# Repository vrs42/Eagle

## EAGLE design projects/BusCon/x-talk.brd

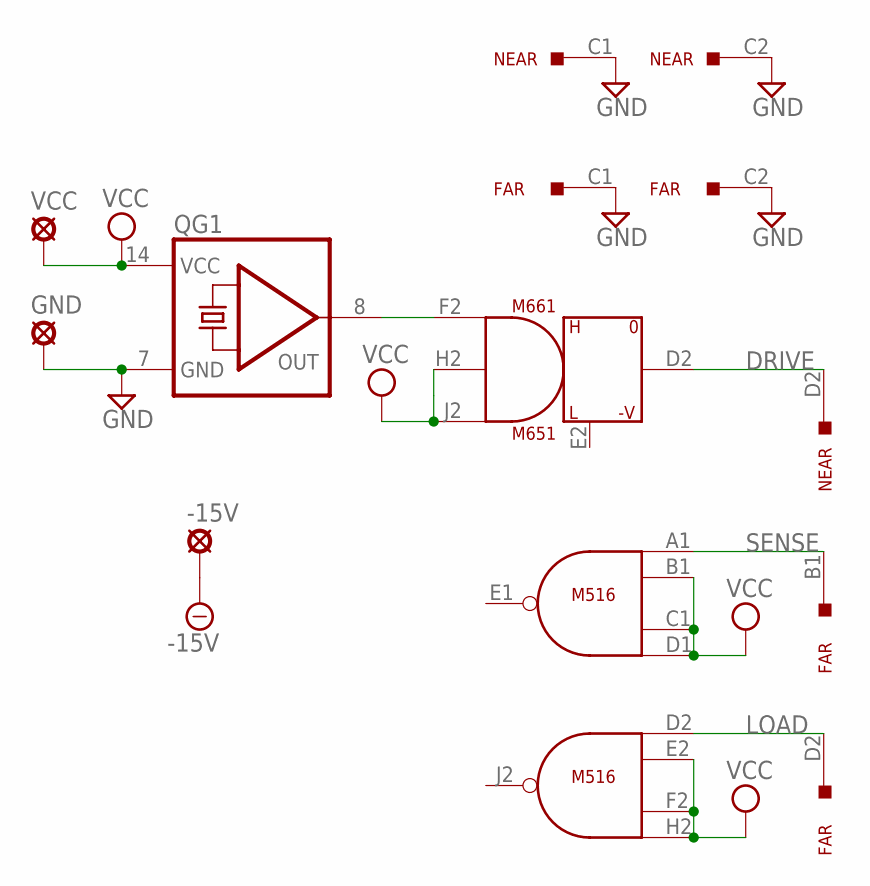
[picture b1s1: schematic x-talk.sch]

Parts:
-15V: SE11
FAR: M916; H807
GND: SE11
M516: M117; H807
M661: M651; H807
NEAR: M916; H807
QG1: QG5860; DIL14S
VCC: SE11

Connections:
-15V: -15V.MP, M661.B2 (-15V)
DRIVE: M661.D2 (OUT), NEAR.D2
GND: FAR.C1, FAR.C2, GND.MP, M516.C2 (GND), M516.T1 (GND), M661.C2 (GND), NEAR.C1, NEAR.C2, QG1.7 (GND)
LOAD: FAR.D2, M516.D2 (IN1)
unnamed: M661.F2 (IN1), QG1.8 (OUT)
SENSE: FAR.B1, M516.A1 (IN1)
VCC: M516.A2 (VCC), M516.B1 (IN2), M516.C1 (IN3), M516.D1 (IN4), M516.E2 (IN2), M516.F2 (IN3), M516.H2 (IN4), M661.A2 (VCC), M661.H2 (IN2), M661.J2 (IN3), QG1.14 (VCC), VCC.MP

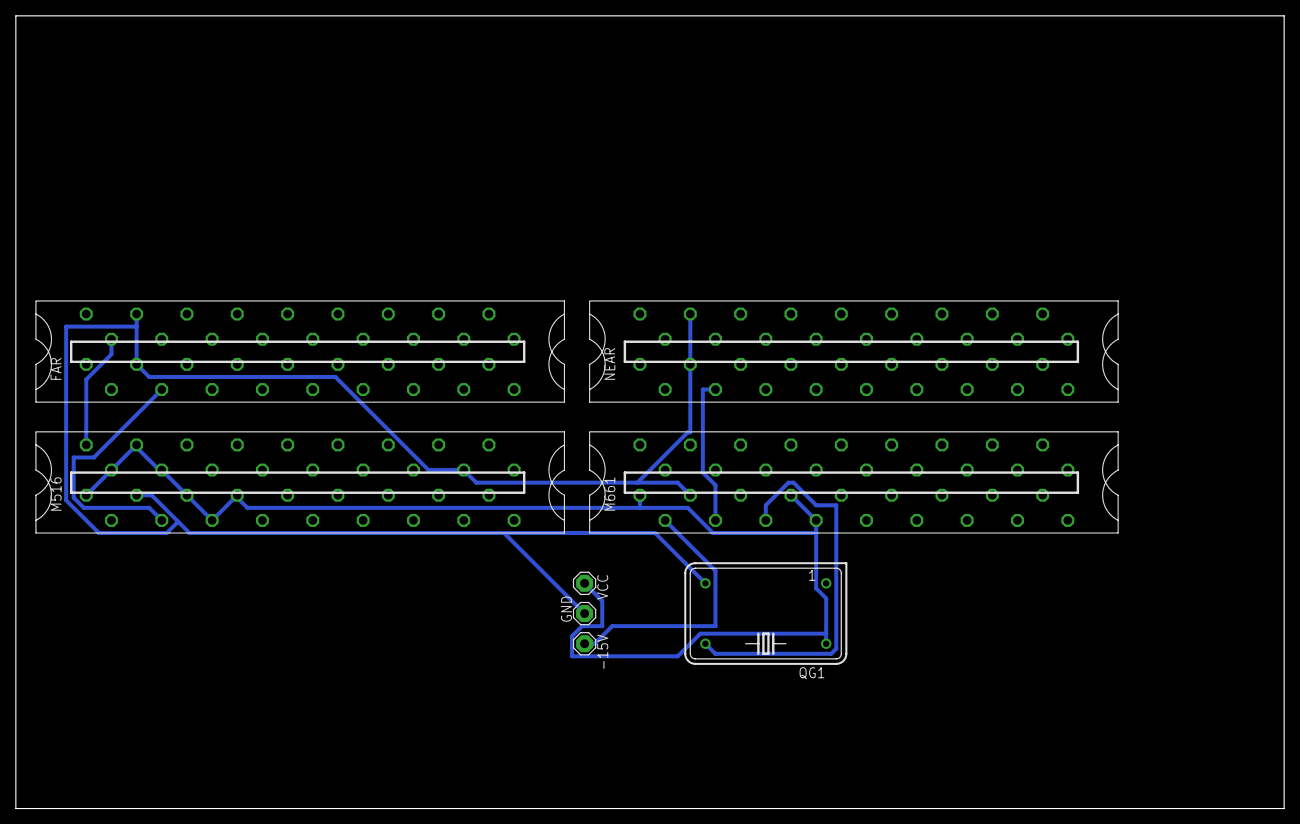
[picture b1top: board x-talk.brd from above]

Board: 2 copper layers, 160.0 x 100.0 mm, 8 parts (0 on the bottom side), 7 nets.

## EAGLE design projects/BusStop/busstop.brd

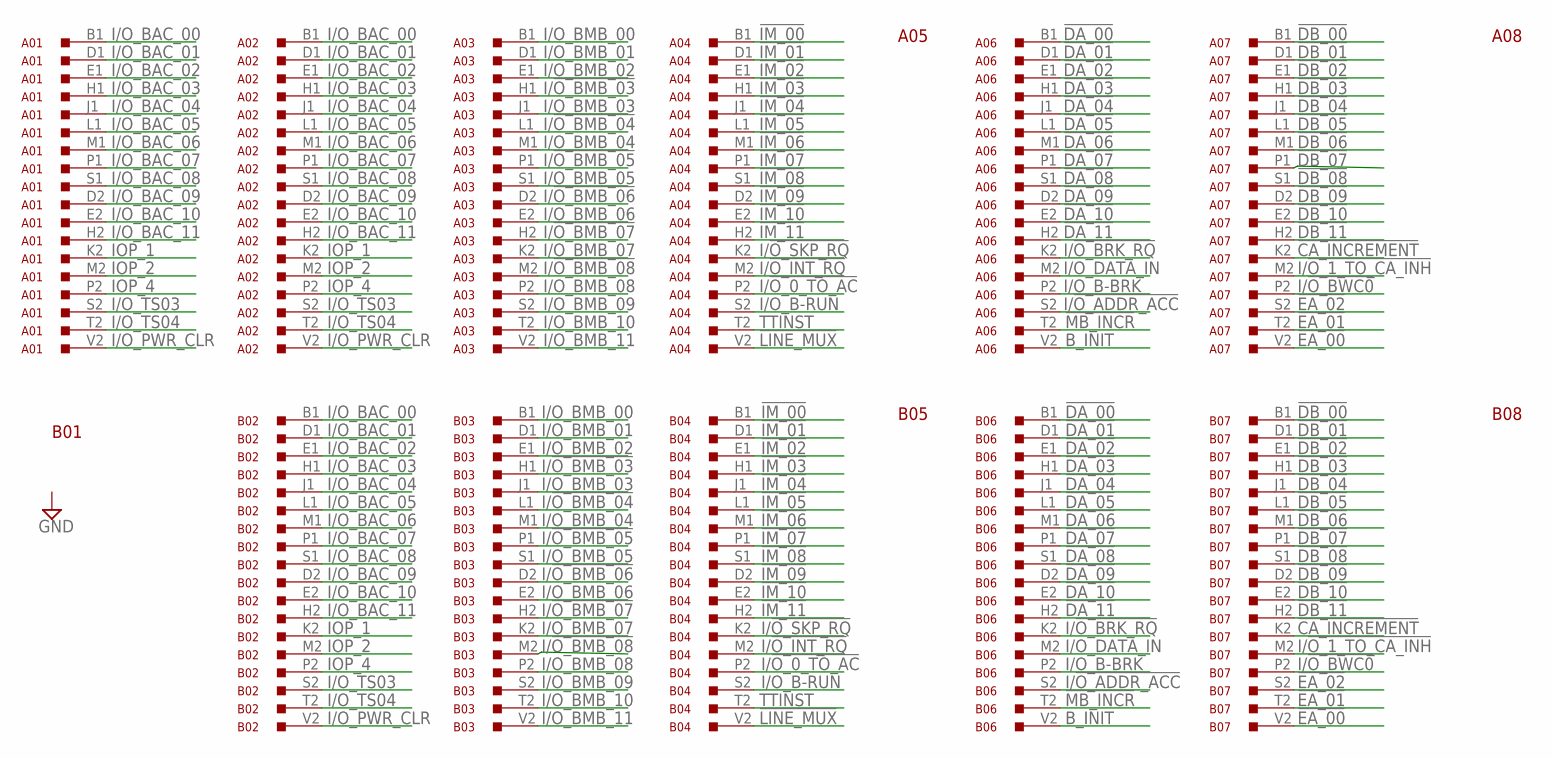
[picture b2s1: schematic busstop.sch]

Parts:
A01: G717; H807
A02, A03, A04, A06, A07: M903; H807
A05, A08: H807
B01, B05, B08: H807
B02, B03, B04, B06, B07: M903; H807

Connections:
!CA_INCREMENT: A07.K2, B07.K2
!DA_00: A06.B1, B06.B1
!DA_01: A06.D1, B06.D1
!DA_02: A06.E1, B06.E1
!DA_03: A06.H1, B06.H1
!DA_04: A06.J1, B06.J1
!DA_05: A06.L1, B06.L1
!DA_06: A06.M1, B06.M1
!DA_07: A06.P1, B06.P1
!DA_08: A06.S1, B06.S1
!DA_09: A06.D2, B06.D2
!DA_10: A06.E2, B06.E2
!DA_11: A06.H2, B06.H2
!DB_00: A07.B1, B07.B1
!DB_01: A07.D1, B07.D1
!DB_02: A07.E1, B07.E1
!DB_03: A07.H1, B07.H1
!DB_04: A07.J1, B07.J1
!DB_05: A07.L1, B07.L1
!DB_06: A07.M1, B07.M1
!DB_07: A07.P1, B07.P1
!DB_08: A07.S1, B07.S1
!DB_09: A07.D2, B07.D2
!DB_10: A07.E2, B07.E2
!DB_11: A07.H2, B07.H2
!EA_00: A07.V2, B07.V2
!EA_01: A07.T2, B07.T2
!EA_02: A07.S2, B07.S2
!IM_00: A04.B1, B04.B1
!IM_01: A04.D1, B04.D1
!IM_02: A04.E1, B04.E1
!IM_03: A04.H1, B04.H1
!IM_04: A04.J1, B04.J1
!IM_05: A04.L1, B04.L1
!IM_06: A04.M1, B04.M1
!IM_07: A04.P1, B04.P1
!IM_08: A04.S1, B04.S1
!IM_09: A04.D2, B04.D2
!IM_10: A04.E2, B04.E2
!IM_11: A04.H2, B04.H2
!LINE_MUX: A04.V2, B04.V2
!MB_INCR: A06.T2, B06.T2
B_INIT: A06.V2, B06.V2
GND: A01.A1 (GND), A01.C1 (GND), A01.C2 (GND), A01.F1 (GND), A01.F2 (GND), A01.J2 (GND), A01.K1 (GND), A01.L2 (GND), A01.N1 (GND), A01.N2 (GND), A01.R1 (GND), A01.R2 (GND), A01.T1 (GND), A01.U2 (GND), A02.A1 (GND), A02.C1 (GND), A02.C2 (GND), A02.F1 (GND), A02.F2 (GND), A02.J2 (GND), A02.K1 (GND), A02.L2 (GND), A02.N1 (GND), A02.N2 (GND), A02.R1 (GND), A02.R2 (GND), A02.T1 (GND), A02.U2 (GND), A03.A1 (GND), A03.C1 (GND), A03.C2 (GND), A03.F1 (GND), A03.F2 (GND), A03.J2 (GND), A03.K1 (GND), A03.L2 (GND), A03.N1 (GND), A03.N2 (GND), A03.R1 (GND), A03.R2 (GND), A03.T1 (GND), A03.U2 (GND), A04.A1 (GND), A04.C1 (GND), A04.C2 (GND), A04.F1 (GND), A04.F2 (GND), A04.J2 (GND), A04.K1 (GND), A04.L2 (GND), A04.N1 (GND), A04.N2 (GND), A04.R1 (GND), A04.R2 (GND), A04.T1 (GND), A04.U2 (GND), A06.A1 (GND), A06.C1 (GND), A06.C2 (GND), A06.F1 (GND), A06.F2 (GND), A06.J2 (GND), A06.K1 (GND), A06.L2 (GND), A06.N1 (GND), A06.N2 (GND), A06.R1 (GND), A06.R2 (GND), A06.T1 (GND), A06.U2 (GND), A07.A1 (GND), A07.C1 (GND), A07.C2 (GND), A07.F1 (GND), A07.F2 (GND), A07.J2 (GND), A07.K1 (GND), A07.L2 (GND), A07.N1 (GND), A07.N2 (GND), A07.R1 (GND), A07.R2 (GND), A07.T1 (GND), A07.U2 (GND), B02.A1 (GND), B02.C1 (GND), B02.C2 (GND), B02.F1 (GND), B02.F2 (GND), B02.J2 (GND), B02.K1 (GND), B02.L2 (GND), B02.N1 (GND), B02.N2 (GND), B02.R1 (GND), B02.R2 (GND), B02.T1 (GND), B02.U2 (GND), B03.A1 (GND), B03.C1 (GND), B03.C2 (GND), B03.F1 (GND), B03.F2 (GND), B03.J2 (GND), B03.K1 (GND), B03.L2 (GND), B03.N1 (GND), B03.N2 (GND), B03.R1 (GND), B03.R2 (GND), B03.T1 (GND), B03.U2 (GND), B04.A1 (GND), B04.C1 (GND), B04.C2 (GND), B04.F1 (GND), B04.F2 (GND), B04.J2 (GND), B04.K1 (GND), B04.L2 (GND), B04.N1 (GND), B04.N2 (GND), B04.R1 (GND), B04.R2 (GND), B04.T1 (GND), B04.U2 (GND), B06.A1 (GND), B06.C1 (GND), B06.C2 (GND), B06.F1 (GND), B06.F2 (GND), B06.J2 (GND), B06.K1 (GND), B06.L2 (GND), B06.N1 (GND), B06.N2 (GND), B06.R1 (GND), B06.R2 (GND), B06.T1 (GND), B06.U2 (GND), B07.A1 (GND), B07.C1 (GND), B07.C2 (GND), B07.F1 (GND), B07.F2 (GND), B07.J2 (GND), B07.K1 (GND), B07.L2 (GND), B07.N1 (GND), B07.N2 (GND), B07.R1 (GND), B07.R2 (GND), B07.T1 (GND), B07.U2 (GND)
I/!O_0_TO_AC: A04.P2, B04.P2
I/!O_1_TO_CA_INH: A07.M2, B07.M2
I/!O_ADDR_ACC: A06.S2, B06.S2
I/!O_BMB_03: A03.H1, B03.H1
I/!O_BMB_04: A03.L1, B03.L1
I/!O_BMB_05: A03.P1, B03.P1
I/!O_BMB_06: A03.D2, B03.D2
I/!O_BMB_07: A03.H2, B03.H2
I/!O_BMB_08: A03.M2, B03.M2
I/!O_BRK_RQ: A06.K2, B06.K2
I/!O_BWC0: A07.P2, B07.P2
I/!O_INT_RQ: A04.M2, B04.M2
I/!O_SKP_RQ: A04.K2, B04.K2
I/O_B-BRK: A06.P2, B06.P2
I/O_B-RUN: A04.S2, B04.S2
I/O_BAC_00: A01.B1, A02.B1, B02.B1
I/O_BAC_01: A01.D1, A02.D1, B02.D1
I/O_BAC_02: A01.E1, A02.E1, B02.E1
I/O_BAC_03: A01.H1, A02.H1, B02.H1
I/O_BAC_04: A01.J1, A02.J1, B02.J1
I/O_BAC_05: A01.L1, A02.L1, B02.L1
I/O_BAC_06: A01.M1, A02.M1, B02.M1
I/O_BAC_07: A01.P1, A02.P1, B02.P1
I/O_BAC_08: A01.S1, A02.S1, B02.S1
I/O_BAC_09: A01.D2, A02.D2, B02.D2
I/O_BAC_10: A01.E2, A02.E2, B02.E2
I/O_BAC_11: A01.H2, A02.H2, B02.H2
I/O_BMB_00: A03.B1, B03.B1
I/O_BMB_01: A03.D1, B03.D1
I/O_BMB_02: A03.E1, B03.E1
I/O_BMB_03: A03.J1, B03.J1
I/O_BMB_04: A03.M1, B03.M1
I/O_BMB_05: A03.S1, B03.S1
I/O_BMB_06: A03.E2, B03.E2
I/O_BMB_07: A03.K2, B03.K2
I/O_BMB_08: A03.P2, B03.P2
I/O_BMB_09: A03.S2, B03.S2
I/O_BMB_10: A03.T2, B03.T2
I/O_BMB_11: A03.V2, B03.V2
I/O_DATA_IN: A06.M2, B06.M2
I/O_PWR_CLR: A01.V2, A02.V2, B02.V2
I/O_TS03: A01.S2, A02.S2, B02.S2
I/O_TS04: A01.T2, A02.T2, B02.T2
IOP_1: A01.K2, A02.K2, B02.K2
IOP_2: A01.M2, A02.M2, B02.M2
IOP_4: A01.P2, A02.P2, B02.P2
TTINST: A04.T2, B04.T2

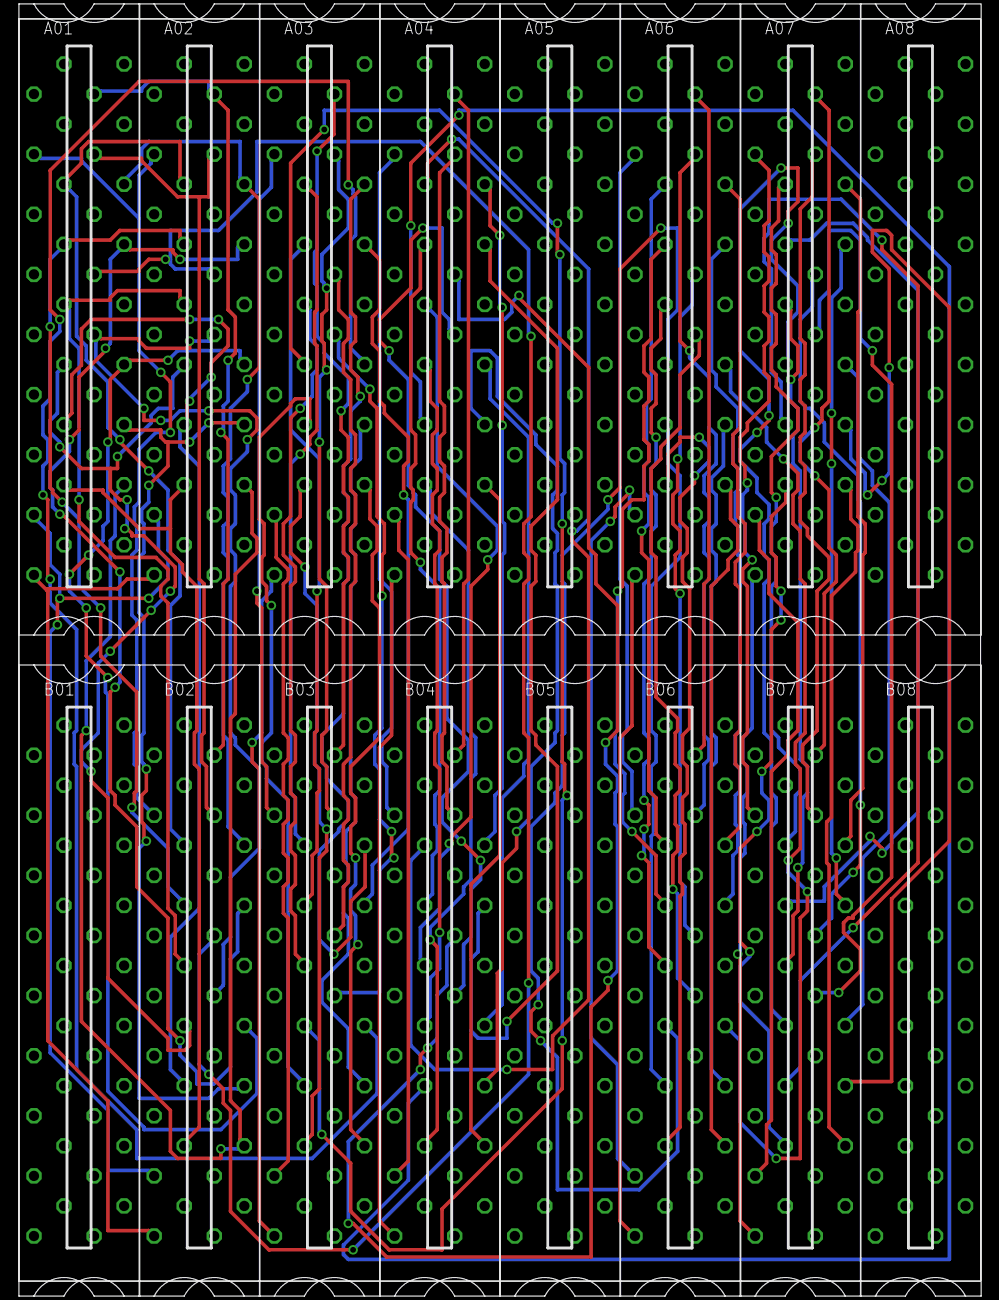
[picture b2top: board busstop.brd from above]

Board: 3 copper layers, 101.6 x 133.3 mm, 18 parts (0 on the bottom side), 91 nets.

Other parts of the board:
U$5, U$6: CBLOCK

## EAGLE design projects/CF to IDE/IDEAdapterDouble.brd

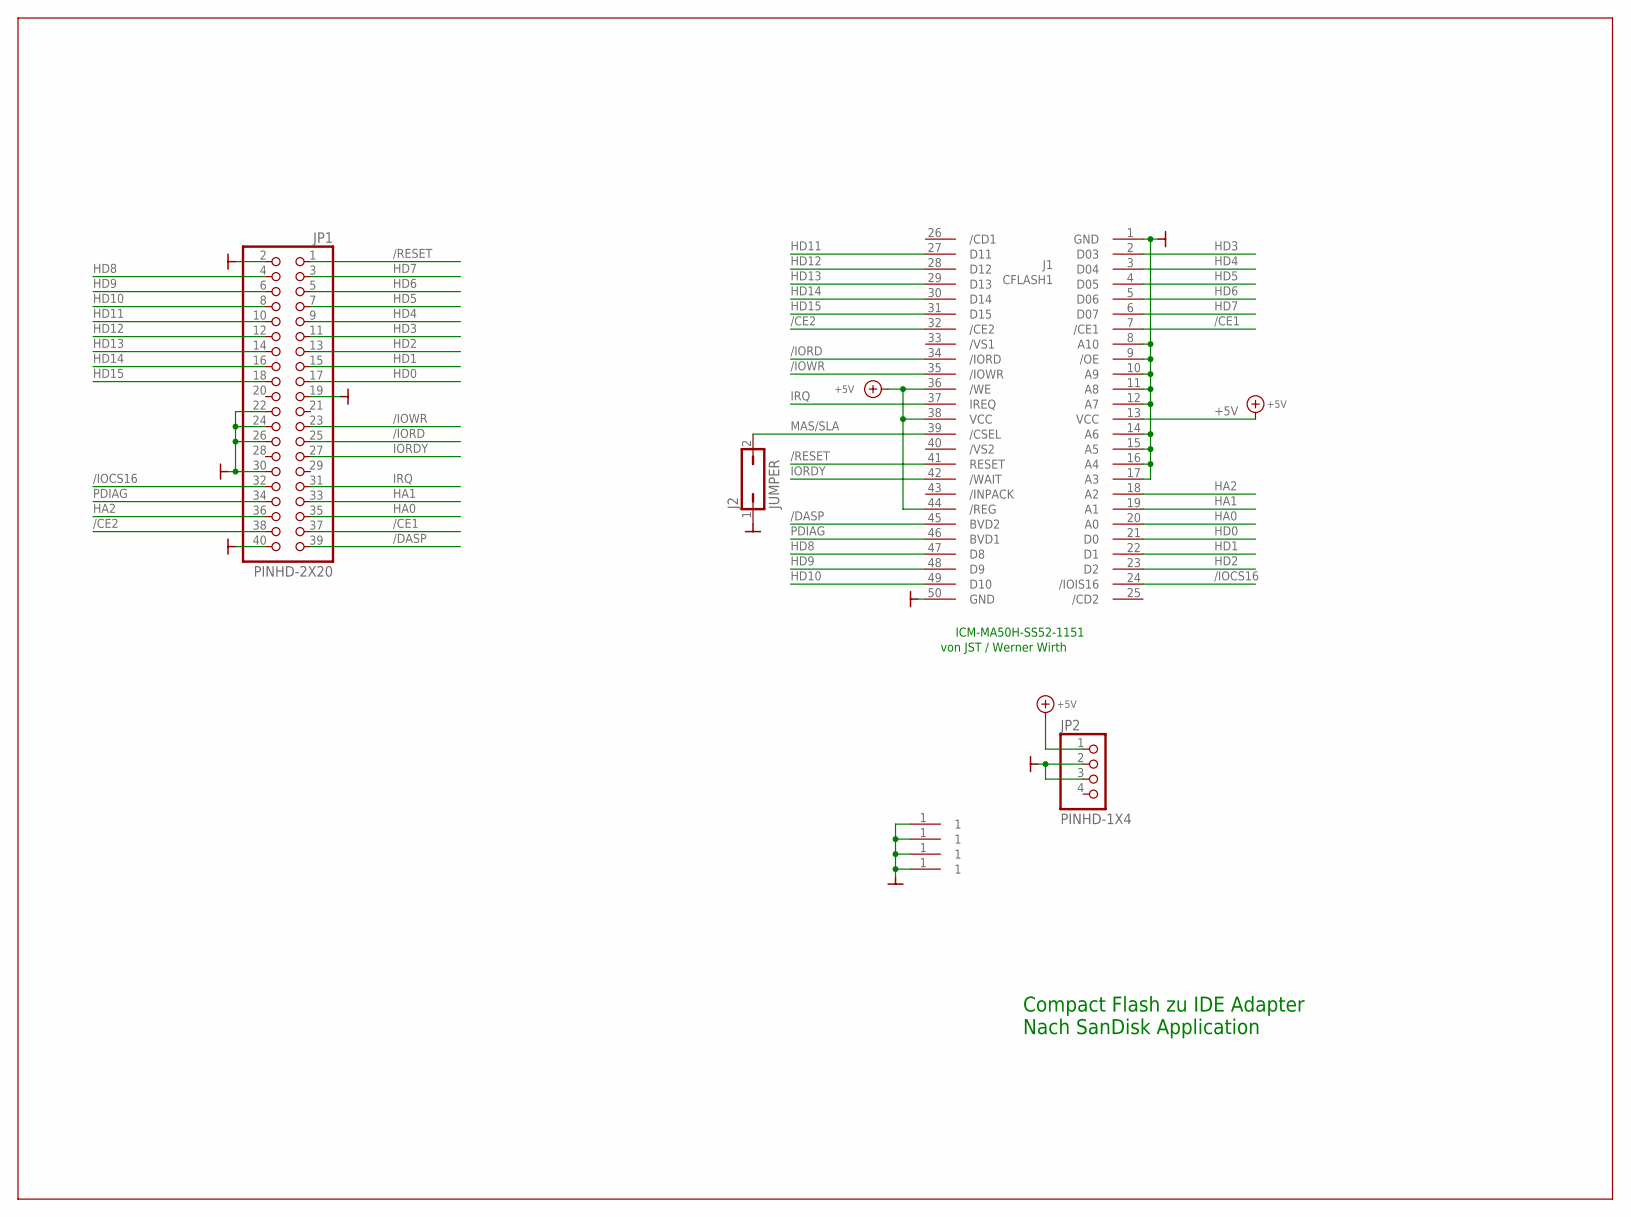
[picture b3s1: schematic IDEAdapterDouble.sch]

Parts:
J1: CFLASH1; CFSMT
J2: JUMPER; JP1
JP1: PINHD-2X20; 2X20
JP2: PINHD-1X4; 1X04
U$13, U$14, U$16, U$17: BOHRUNG

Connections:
+5V: J1.13 (VCC), J1.36 (/WE), J1.38 (VCC), J1.44 (/REG), JP2.1
/CE1: J1.7 (/CE1), JP1.37
/CE2: J1.32 (/CE2), JP1.38
/DASP: J1.45 (BVD2), JP1.39
/IOCS16: J1.24 (/IOIS16), JP1.32
/IORD: J1.34 (/IORD), JP1.25
/IOWR: J1.35 (/IOWR), JP1.23
/RESET: J1.41 (RESET), JP1.1
GND: J1.1 (GND), J1.8 (A10), J1.9 (/OE), J1.10 (A9), J1.11 (A8), J1.12 (A7), J1.14 (A6), J1.15 (A5), J1.16 (A4), J1.17 (A3), J1.50 (GND), J2.1, JP1.2, JP1.19, JP1.22, JP1.24, JP1.26, JP1.30, JP1.40, JP2.2, JP2.3, U$13.1, U$14.1, U$16.1, U$17.1
HA0: J1.20 (A0), JP1.35
HA1: J1.19 (A1), JP1.33
HA2: J1.18 (A2), JP1.36
HD0: J1.21 (D0), JP1.17
HD1: J1.22 (D1), JP1.15
HD2: J1.23 (D2), JP1.13
HD3: J1.2 (D03), JP1.11
HD4: J1.3 (D04), JP1.9
HD5: J1.4 (D05), JP1.7
HD6: J1.5 (D06), JP1.5
HD7: J1.6 (D07), JP1.3
HD8: J1.47 (D8), JP1.4
HD9: J1.48 (D9), JP1.6
HD10: J1.49 (D10), JP1.8
HD11: J1.27 (D11), JP1.10
HD12: J1.28 (D12), JP1.12
HD13: J1.29 (D13), JP1.14
HD14: J1.30 (D14), JP1.16
HD15: J1.31 (D15), JP1.18
IORDY: J1.42 (/WAIT), JP1.27
IRQ: J1.37 (IREQ), JP1.31
MAS/SLA: J1.39 (/CSEL), J2.2
PDIAG: J1.46 (BVD1), JP1.34

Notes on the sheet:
Compact Flash zu IDE Adapter
Nach SanDisk Application
ICM-MA50H-SS52-1151
von JST / Werner Wirth

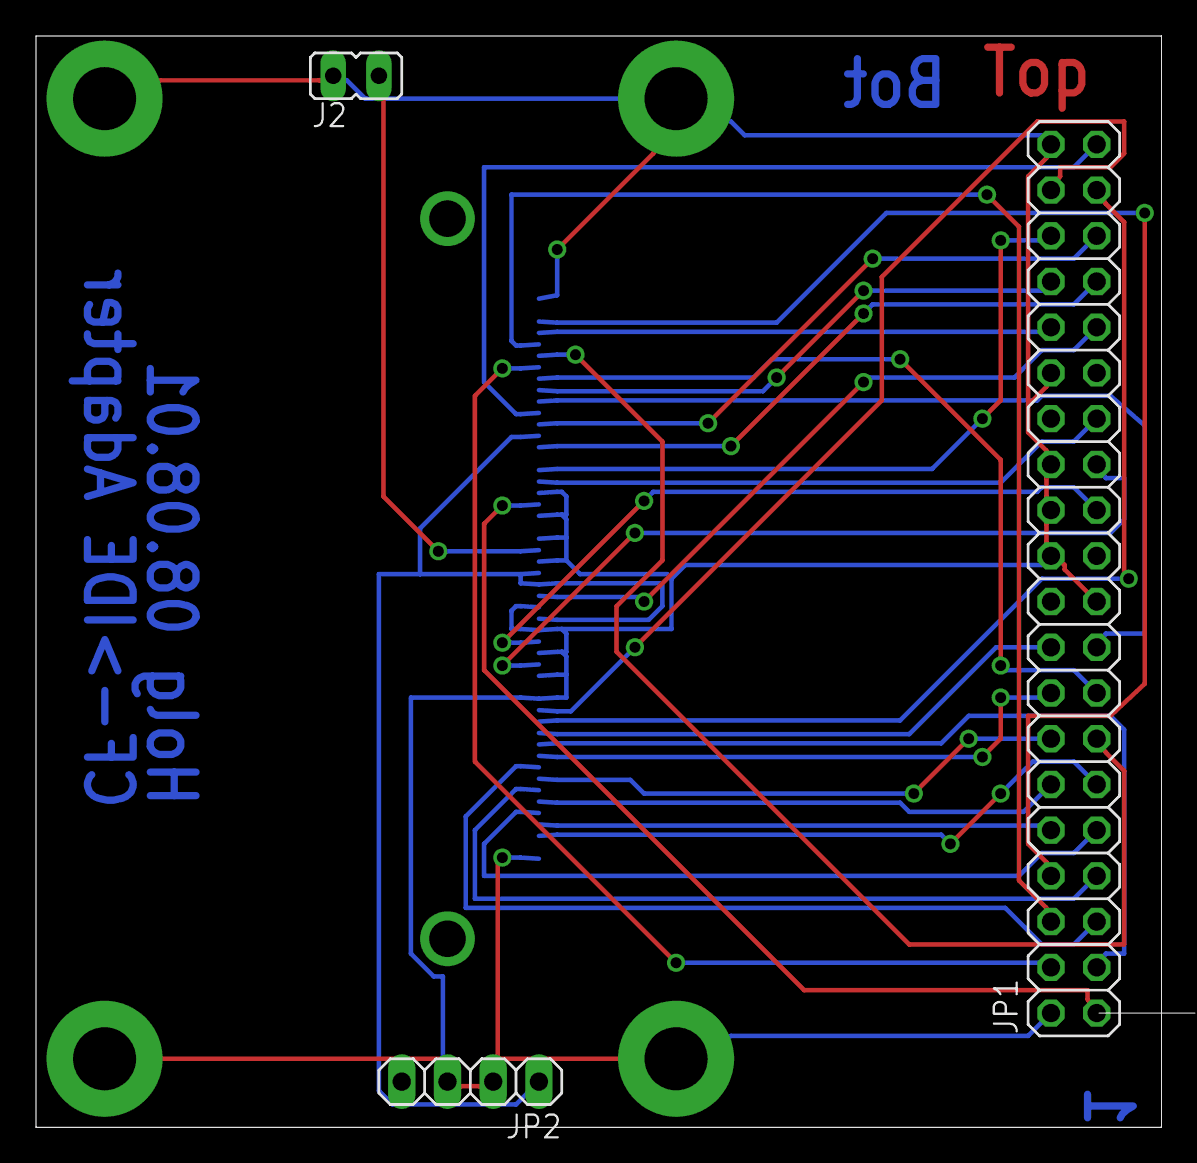
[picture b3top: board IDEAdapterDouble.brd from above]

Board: 2 copper layers, 62.5 x 60.6 mm, 8 parts (1 on the bottom side), 32 nets.

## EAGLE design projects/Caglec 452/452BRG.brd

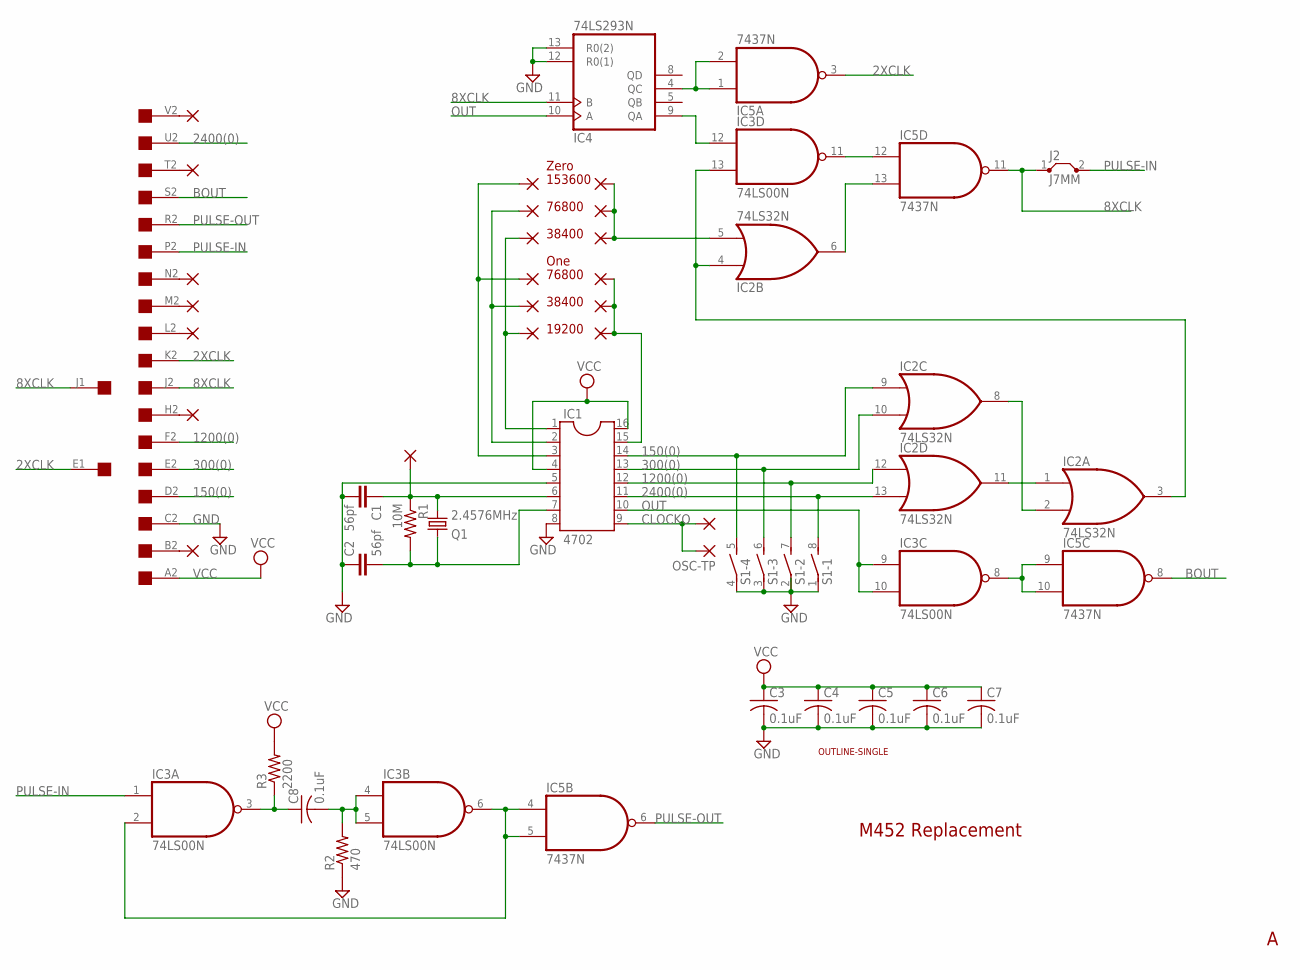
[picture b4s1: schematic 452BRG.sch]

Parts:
C1, C2: 56pf; C075-032X103
C3, C4, C5, C6, C7, C8: 0.1uF; C075-032X103
IC1: 4702; DIL16
IC2: 74LS32N; DIL14
IC3: 74LS00N; DIL14
IC4: 74LS293N; DIL14
IC5: 7437N; DIL14
J2: J7MM; 07
OSC-TP: 1,6/0,8
PAD1, PAD2, PAD3, PAD4, PAD5, PAD6, PAD7, PAD8, PAD9, PAD10, PAD11, PAD12, PAD13, PAD14, PAD15, PAD16, PAD17, PAD18, PAD19, PAD20: 1,6/0,8
Q1: 2.4576MHz; HC49U-H
R1: 10M; 0207/10
R2: 470; 0207/12
R3: 2200; 0207/15
S1: DIP04S
U$2: SINGLE; EDGE-CON2
U$3: OUTLINE-SINGLE; SINGLE
XTAL: 1,6/0,8

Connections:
2XCLK: IC5.3 (O), U$2.E1, U$2.K2
8XCLK: IC4.11 (B), IC5.11 (O), J2.1, U$2.J1, U$2.J2
150(0): IC1.14, IC2.9 (I0), S1.5 (2), U$2.D2
300(0): IC1.13, IC2.10 (I1), S1.6 (2), U$2.E2
1200(0): IC1.12, IC2.12 (I0), S1.7 (2), U$2.F2
2400(0): IC1.11, IC2.13 (I1), S1.8 (2), U$2.U2
!OUT: IC3.8 (O), IC5.9 (I0), IC5.10 (I1)
BOUT: IC5.8 (O), U$2.S2
CLOCKO: IC1.9, OSC-TP.1, PAD20.1
GND: C1.2, C2.1, C3.2, C4.2, C5.2, C6.2, C7.2, IC1.5, IC1.8, IC2.7 (GND), IC3.7 (GND), IC4.7 (GND), IC4.12 (R0(1)), IC4.13 (R0(2)), IC5.7 (GND), R2.1, S1.1, S1.2 (1), S1.3 (1), S1.4 (1), U$2.C2
unnamed: C2.2, IC1.7, Q1.1, R1.2
unnamed: IC2.1 (I0), IC2.11 (O)
unnamed: IC1.15, PAD4.1, PAD5.1, PAD6.1
unnamed: IC2.2 (I1), IC2.8 (O)
unnamed: IC1.3, PAD1.1, PAD7.1
unnamed: IC1.1, PAD3.1, PAD9.1
unnamed: IC1.2, PAD2.1, PAD8.1
unnamed: IC2.3 (O), IC2.4 (I0), IC3.13 (I1)
unnamed: IC2.5 (I1), PAD10.1, PAD11.1, PAD12.1
unnamed: IC4.4 (QC), IC5.1 (I0), IC5.2 (I1)
unnamed: IC3.12 (I0), IC4.9 (QA)
unnamed: C8.2, IC3.4 (I0), IC3.5 (I1), R2.2
unnamed: IC3.2 (I1), IC3.6 (O), IC5.4 (I0), IC5.5 (I1)
unnamed: IC3.11 (O), IC5.12 (I0)
unnamed: IC2.6 (O), IC5.13 (I1)
unnamed: C8.1, IC3.3 (O), R3.1
unnamed: C1.1, IC1.6, Q1.2, R1.1, XTAL.1
unnamed: PAD13.1, U$2.V2
unnamed: PAD14.1, U$2.T2
unnamed: PAD15.1, U$2.N2
unnamed: PAD16.1, U$2.M2
unnamed: PAD17.1, U$2.L2
unnamed: PAD18.1, U$2.H2
unnamed: PAD19.1, U$2.B2
OUT: IC1.10, IC3.9 (I0), IC3.10 (I1), IC4.10 (A)
PULSE-IN: IC3.1 (I0), J2.2, U$2.P2
PULSE-OUT: IC5.6 (O), U$2.R2
VCC: C3.1, C4.1, C5.1, C6.1, C7.1, IC1.4, IC1.16, IC2.14 (VCC), IC3.14 (VCC), IC4.14 (VCC), IC5.14 (VCC), R3.2, U$2.A2

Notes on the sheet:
M452 Replacement
76800
38400
19200
153600
Zero
One

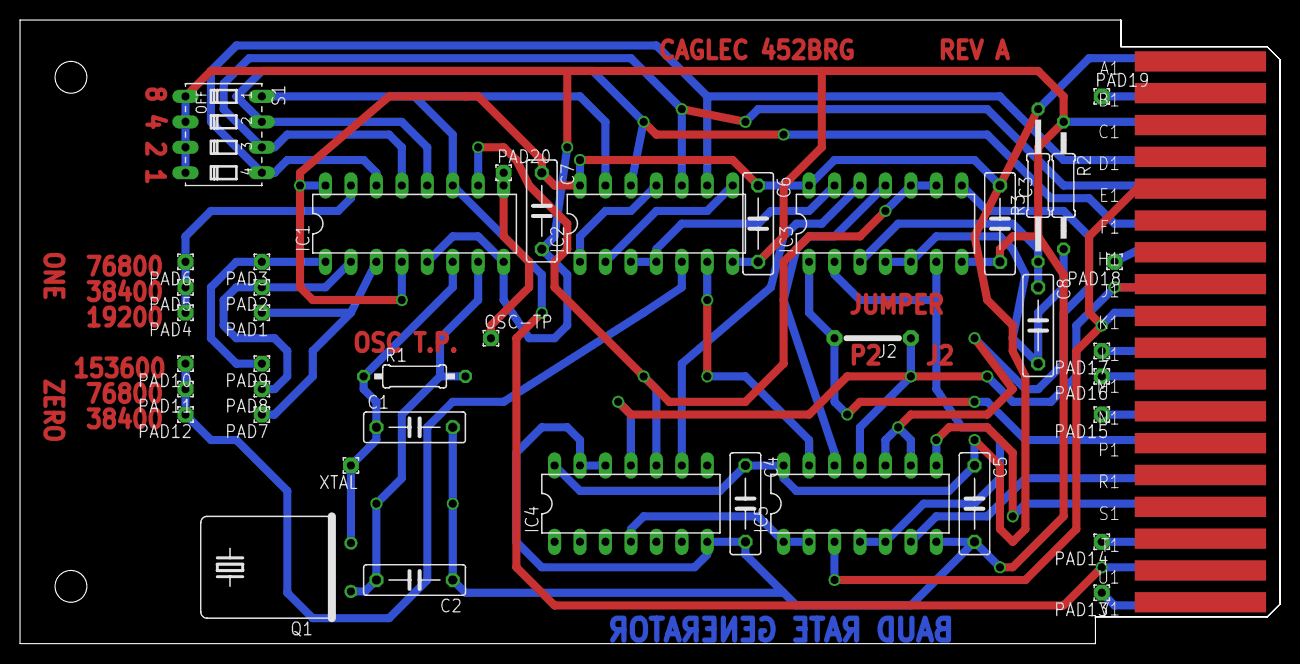
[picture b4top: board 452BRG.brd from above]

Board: 2 copper layers, 125.7 x 62.2 mm, 43 parts (0 on the bottom side), 38 nets.

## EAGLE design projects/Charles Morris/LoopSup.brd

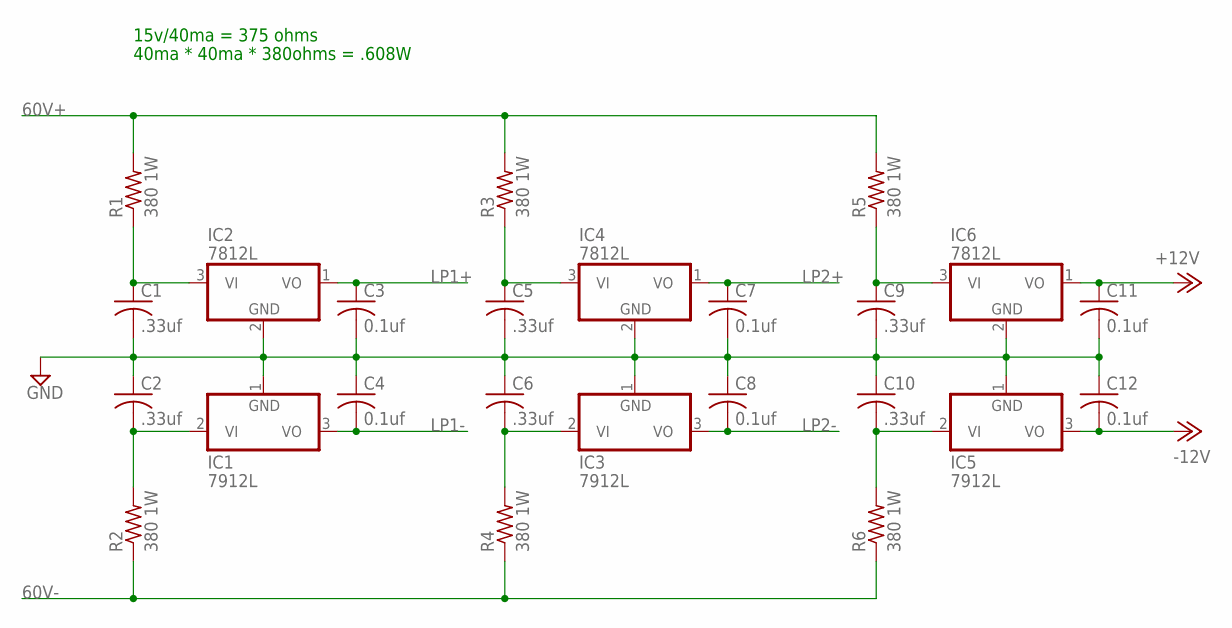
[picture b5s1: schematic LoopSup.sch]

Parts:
C1, C2, C5, C6, C9, C10: .33uf; C050-025X075
C3, C4, C7, C8, C11, C12: 0.1uf; C050-025X075
IC1, IC3, IC5: 7912L; TO92
IC2, IC4, IC6: 7812L; TO92
R1, R2, R3, R4, R5, R6: 380 1W; 0309/12

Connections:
60V+: R1.2, R3.2, R5.2
60V-: R2.1, R4.1, R6.1
+12V: C11.1, IC6.1 (VO)
-12V: C12.2, IC5.3 (VO)
GND: C1.2, C2.1, C3.2, C4.1, C5.2, C6.1, C7.2, C8.1, C9.2, C10.1, C11.2, C12.1, IC1.1 (GND), IC2.2 (GND), IC3.1 (GND), IC4.2 (GND), IC5.1 (GND), IC6.2 (GND)
LP1+: C3.1, IC2.1 (VO)
LP1-: C4.2, IC1.3 (VO)
LP2+: C7.1, IC4.1 (VO)
LP2-: C8.2, IC3.3 (VO)
unnamed: C6.2, IC3.2 (VI), R4.2
unnamed: C2.2, IC1.2 (VI), R2.2
unnamed: C1.1, IC2.3 (VI), R1.1
unnamed: C5.1, IC4.3 (VI), R3.1
unnamed: C10.2, IC5.2 (VI), R6.2
unnamed: C9.1, IC6.3 (VI), R5.1

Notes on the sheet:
15v/40ma = 375 ohms
40ma * 40ma * 380ohms = .608W

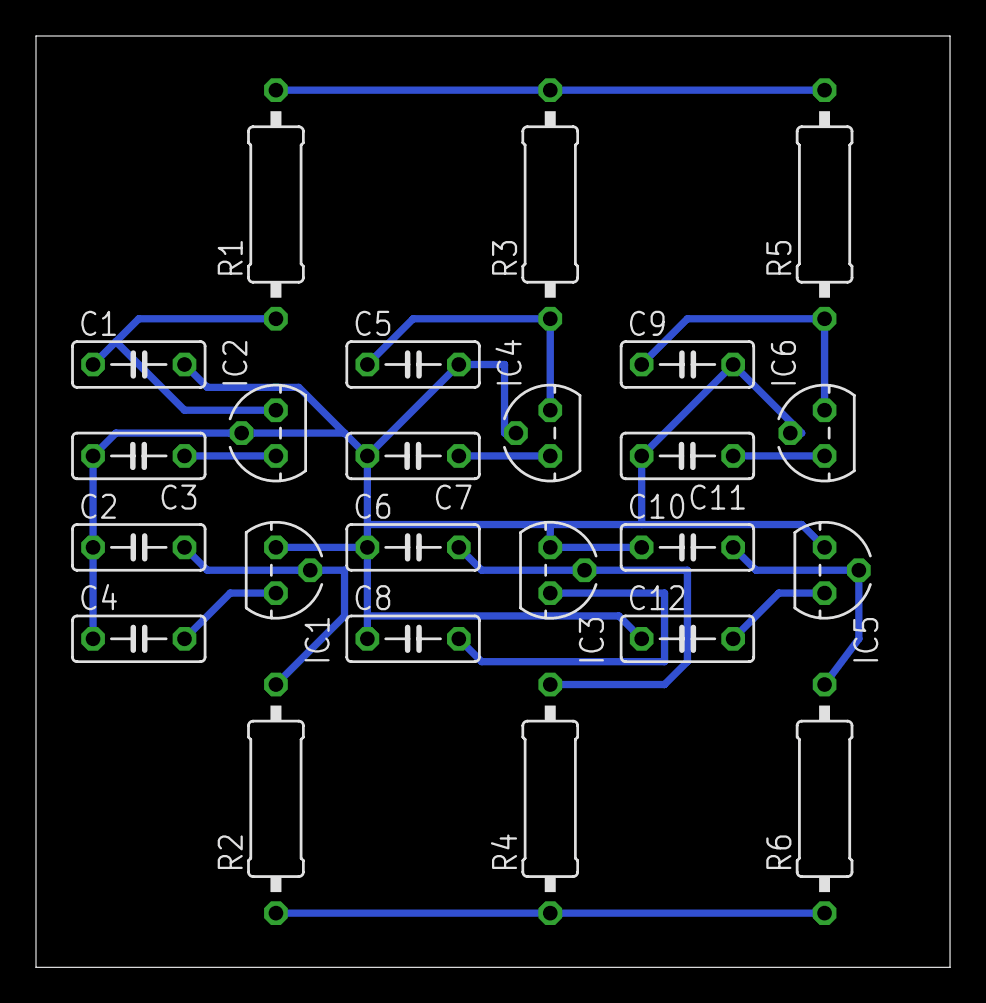
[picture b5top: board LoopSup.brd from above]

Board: 2 copper layers, 50.8 x 51.7 mm, 24 parts (0 on the bottom side), 15 nets.

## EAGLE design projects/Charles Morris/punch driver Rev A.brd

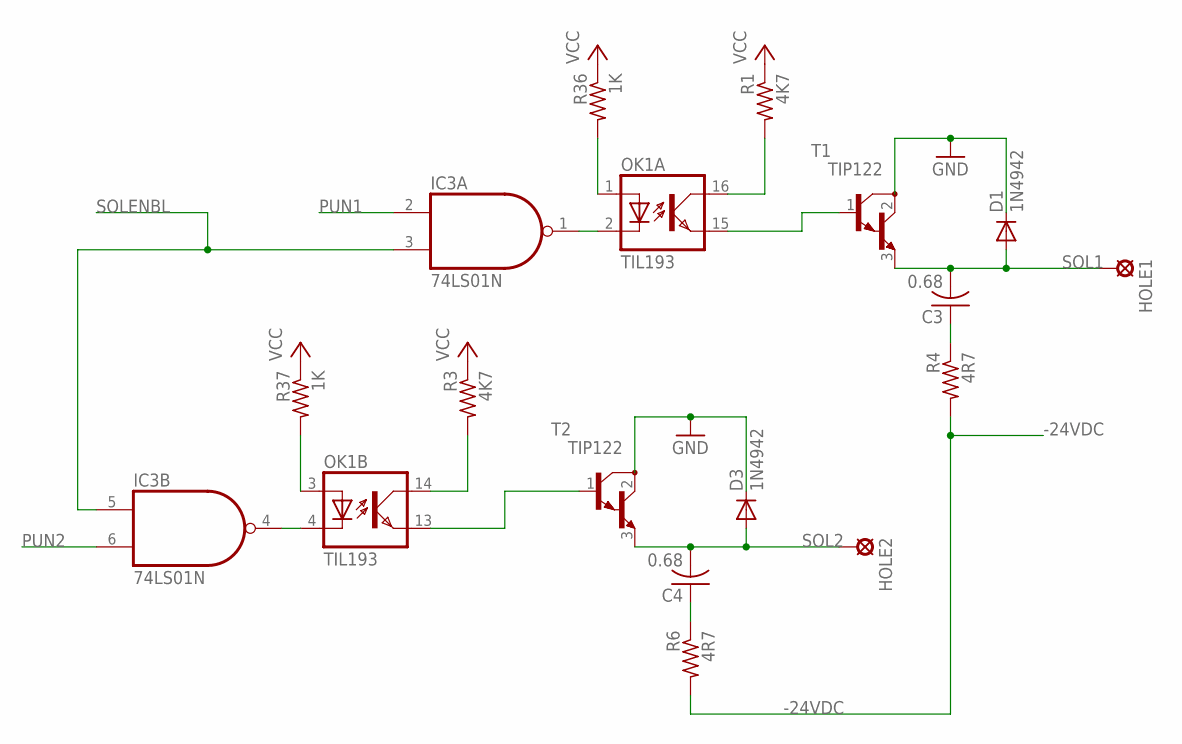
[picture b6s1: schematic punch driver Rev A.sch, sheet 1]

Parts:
C3, C4: 0.68; C075-042X103
D1, D3: 1N4942; DO41-10
HOLE1, HOLE2: SE13
IC3: 74LS01N; DIL14
OK1: TIL193; DIL16
R1, R3: 4K7; 0204/5
R4, R6: 4R7; 0207/10
R36, R37: 1K; 0204/5
T1, T2: TIP122; TO220

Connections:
-24VDC: R4.2, R6.2; also elsewhere on the board
GND: D1.C, D3.C, T1.2 (C), T2.2 (C); also elsewhere on the board
unnamed: OK1.15 (EMIT), T1.1 (B)
unnamed: OK1.14 (COL), R3.2
unnamed: C3.1, R4.1
unnamed: C4.1, R6.1
unnamed: IC3.1 (O), OK1.2 (C)
unnamed: IC3.4 (O), OK1.4 (C)
unnamed: OK1.1 (A), R36.2
unnamed: OK1.3 (A), R37.2
unnamed: OK1.16 (COL), R1.2
unnamed: OK1.13 (EMIT), T2.1 (B)
PUN1: IC3.2 (I0); also elsewhere on the board
PUN2: IC3.6 (I1); also elsewhere on the board
SOL1: C3.2, D1.A, HOLE1.MP, T1.3 (E)
SOL2: C4.2, D3.A, HOLE2.MP, T2.3 (E)
SOLENBL: IC3.3 (I1), IC3.5 (I0); also elsewhere on the board
VCC: R1.1, R3.1, R36.1, R37.1; also elsewhere on the board

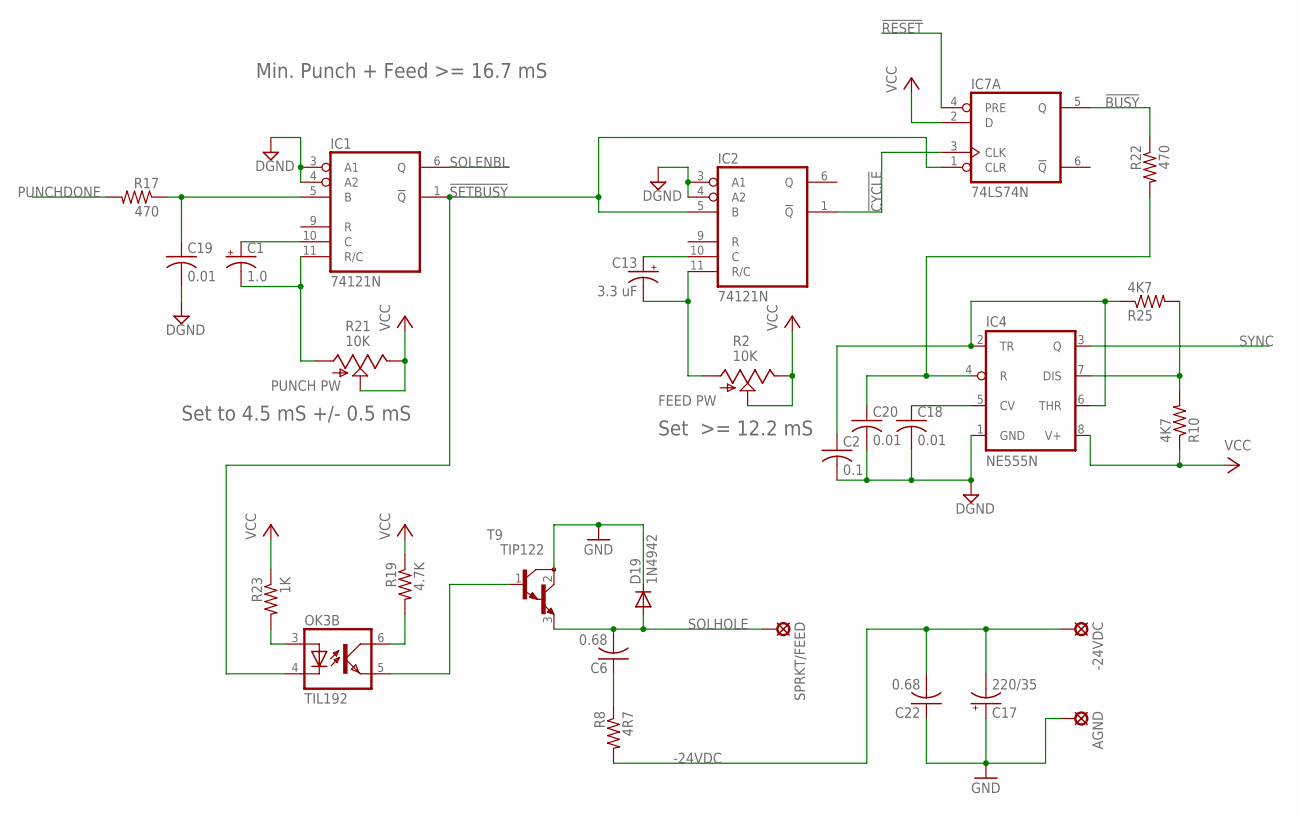
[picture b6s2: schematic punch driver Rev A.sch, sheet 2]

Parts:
-24VDC: SE13
AGND: SE13
C1: 1.0; E5-10,5
C2: 0.1; C050-025X075
C6, C22: 0.68; C075-042X103
C13: 3.3 uF; E5-10,5
C17: 220/35; E25-9
C18, C19, C20: 0.01; C025-025X050
D19: 1N4942; DO41-10
IC1, IC2: 74121N; DIL14
IC4: NE555N; DIL08
IC7: 74LS74N; DIL14
OK3: TIL192; DIL08
R2, R21: 10K; PT-SPIN
R8: 4R7; 0207/10
R10, R25: 4K7; 0204/5
R17, R22: 470; 0204/5
R19: 4.7K; 0204/5
R23: 1K; 0204/5
SPRKT/FEED: SE13
T9: TIP122; TO220

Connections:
!BUSY: IC7.5 (Q), R22.1
!CYCLE: IC2.1 (!Q), IC7.3 (CLK)
!RESET: IC7.4 (PRE); also elsewhere on the board
!SETBUSY: IC1.1 (!Q), IC2.5 (B), IC7.1 (CLR), OK3.4 (C)
-24VDC: -24VDC.MP, C17.-, C22.2, R8.2; also elsewhere on the board
DGND: C2.2, C18.2, C19.2, C20.2, IC1.3 (A1), IC1.4 (A2), IC2.3 (A1), IC2.4 (A2), IC4.1 (GND); also elsewhere on the board
GND: AGND.MP, C17.+, C22.1, D19.C, T9.2 (C); also elsewhere on the board
unnamed: C1.+, IC1.10 (C)
unnamed: IC4.7 (DIS), R10.2, R25.2
unnamed: OK3.6 (COL), R19.2
unnamed: C19.1, IC1.5 (B), R17.1
unnamed: OK3.3 (A), R23.2
unnamed: C1.-, IC1.11 (R/C), R21.A
unnamed: C2.1, IC4.2 (TR), IC4.6 (THR), R25.1
unnamed: C20.1, IC4.4 (R), R22.2
unnamed: C6.1, R8.1
unnamed: C13.+, IC2.10 (C)
unnamed: C13.-, IC2.11 (R/C), R2.A
unnamed: OK3.5 (EMIT), T9.1 (B)
unnamed: C18.1, IC4.5 (CV)
PUNCHDONE: R17.2; also elsewhere on the board
SOLENBL: IC1.6 (Q); also elsewhere on the board
SOLHOLE: C6.2, D19.A, SPRKT/FEED.MP, T9.3 (E)
SYNC: IC4.3 (Q); also elsewhere on the board
VCC: IC4.8 (V+), IC7.2 (D), R2.E, R2.S, R10.1, R19.1, R21.E, R21.S, R23.1; also elsewhere on the board

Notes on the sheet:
PUNCH PW
FEED PW
Set to 4.5 mS +/- 0.5 mS
Set >= 12.2 mS
Min. Punch + Feed >= 16.7 mS

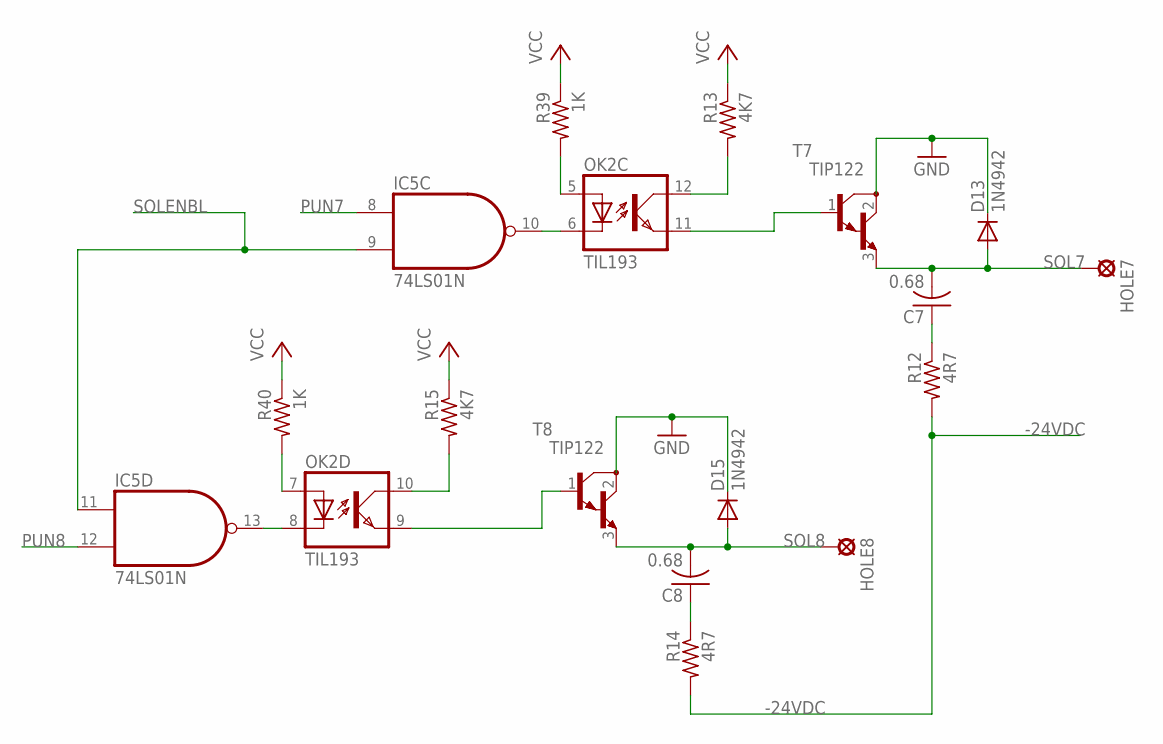
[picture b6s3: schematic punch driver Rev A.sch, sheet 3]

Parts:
C7, C8: 0.68; C075-042X103
D13, D15: 1N4942; DO41-10
HOLE7, HOLE8: SE13
IC5: 74LS01N; DIL14
OK2: TIL193; DIL16
R12, R14: 4R7; 0207/10
R13, R15: 4K7; 0204/5
R39, R40: 1K; 0204/5
T7, T8: TIP122; TO220

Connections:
-24VDC: R12.2, R14.2; also elsewhere on the board
GND: D13.C, D15.C, T7.2 (C), T8.2 (C); also elsewhere on the board
unnamed: OK2.12 (COL), R13.2
unnamed: OK2.10 (COL), R15.2
unnamed: C7.1, R12.1
unnamed: C8.1, R14.1
unnamed: IC5.13 (O), OK2.8 (C)
unnamed: IC5.10 (O), OK2.6 (C)
unnamed: OK2.7 (A), R40.2
unnamed: OK2.5 (A), R39.2
unnamed: OK2.11 (EMIT), T7.1 (B)
unnamed: OK2.9 (EMIT), T8.1 (B)
PUN7: IC5.8 (I0); also elsewhere on the board
PUN8: IC5.12 (I1); also elsewhere on the board
SOL7: C7.2, D13.A, HOLE7.MP, T7.3 (E)
SOL8: C8.2, D15.A, HOLE8.MP, T8.3 (E)
SOLENBL: IC5.9 (I1), IC5.11 (I0); also elsewhere on the board
VCC: R13.1, R15.1, R39.1, R40.1; also elsewhere on the board

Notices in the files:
projects/Charles Morris/punch driver Rev A.brd:
Rev. A (C) 2005 CEMorris
projects/Charles Morris/simple-loop-active.brd:
RS232-Current Loop 20mA (c)2006 CEM & VRS
